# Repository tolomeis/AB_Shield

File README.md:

##AB_Shield

Arduino shield interface for A-BRIDGE

This shield enables you to use the A-BRIDGE module with an Arduino Board in a bunch of seconds. The shield has also a small protoboard area for your custom circuits

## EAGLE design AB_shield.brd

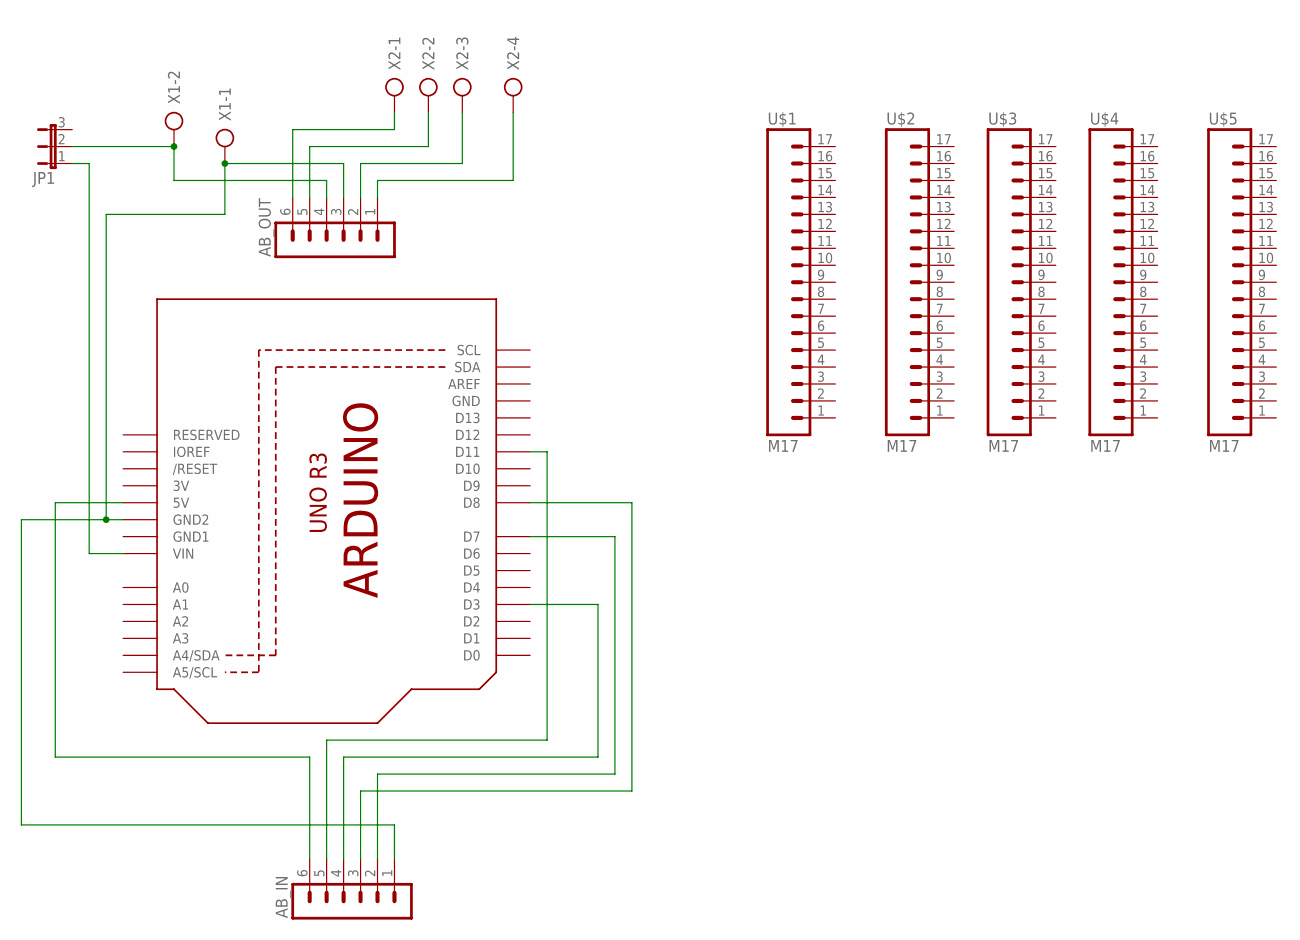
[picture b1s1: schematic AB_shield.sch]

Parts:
AB_IN: MA06-1
AB_OUT: MA06-1
JP1: JP2E; JP2
U1: ARDUINOR3-DIMENSION; ARDUINOR3
U$1, U$2, U$3, U$4, U$5: M17; 1X17_PROTO
X1: AK500/2-H
X2: AK500/4

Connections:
3V: U1.3V
GND: U1.GND
GND1: U1.GND1
unnamed: AB_IN.4, U1.D3
unnamed: AB_IN.5, U1.D11
unnamed: AB_IN.3, U1.D8
unnamed: AB_IN.2, U1.D7
unnamed: AB_IN.6, U1.5V
unnamed: AB_OUT.5, X2.2
unnamed: AB_OUT.6, X2.1
unnamed: AB_OUT.2, X2.3
unnamed: AB_OUT.1, X2.4
unnamed: AB_OUT.4, JP1.2, X1.2
unnamed: AB_IN.1, AB_OUT.3, U1.GND2, X1.1
unnamed: JP1.1, U1.VIN

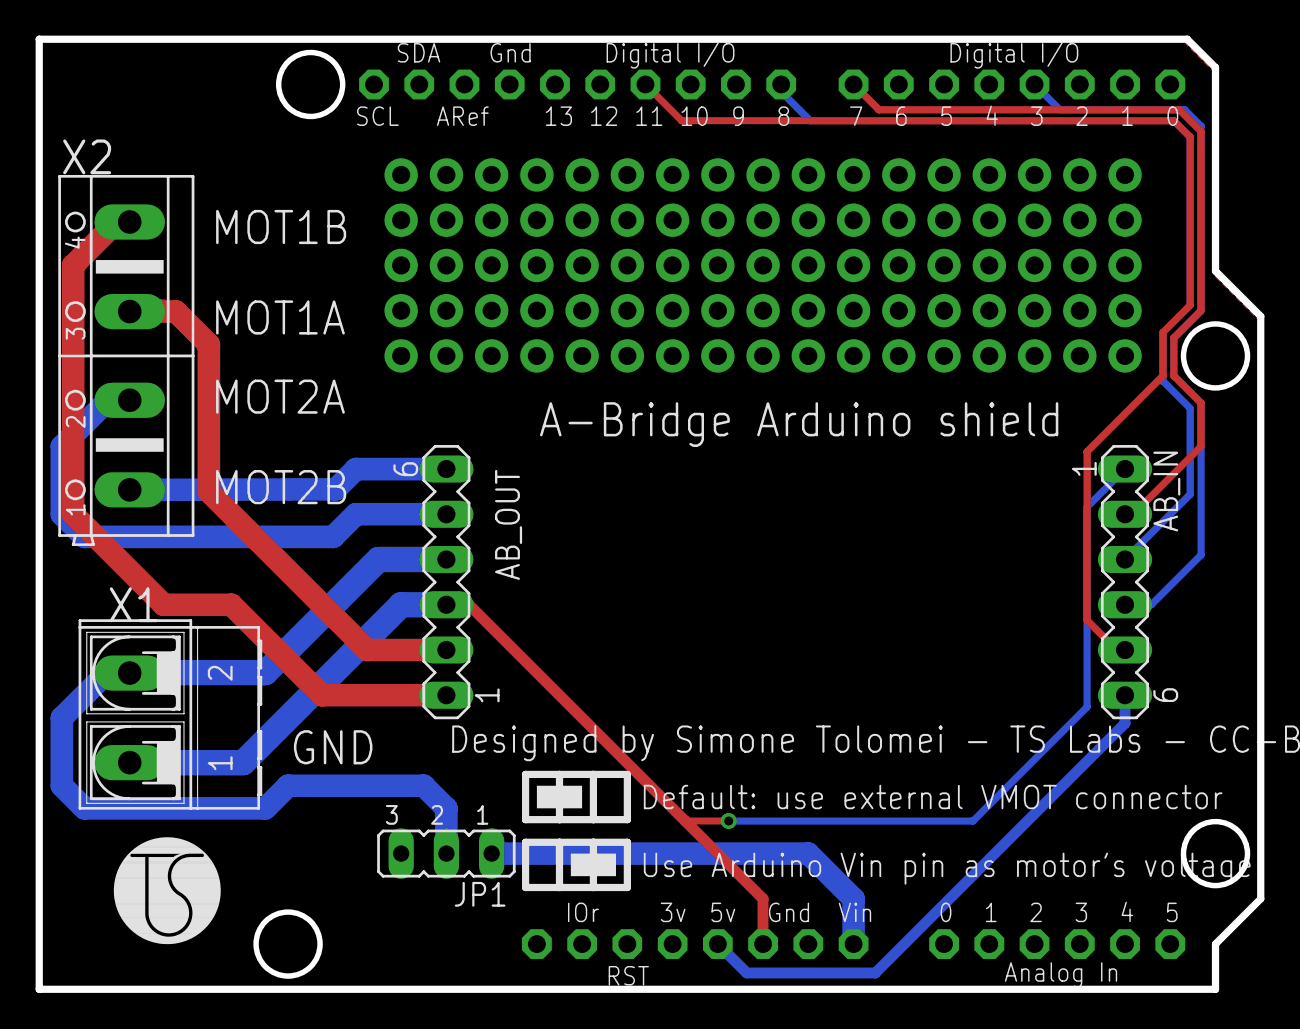
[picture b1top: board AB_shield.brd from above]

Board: 2 copper layers, 68.6 x 53.3 mm, 11 parts (0 on the bottom side), 12 nets.

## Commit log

2016-09-09 :boom::camel: Added .gitattributes & .gitignore files
2016-09-24 Added silkscreen pinout and jumper info
2016-09-24 Added rendering image
2016-12-20 ABridge Shield v1
    Better jumper description
    Added TS logo

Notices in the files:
AB_shield.brd:
Designed by Simone Tolomei - TS Labs - CC-BY-SA
parts and their libraries:
SparkFun_proto: Licensing: CC v3.0 Share-Alike You are welcome to use this library for commercial purposes.
